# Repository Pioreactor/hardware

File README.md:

### HAT hardware setup

#### Installation

0. Install git: `sudo apt-get install git -y`
1. git clone this repo to your Raspberry Pi: `git clone --recurse-submodules https://github.com/Pioreactor/hardware.git && cd hardware`
2. Install eeprom utils: `cd hats/eepromutils && make && sudo make install && cd ..`
3. Move some files over: `mv ../eeprom/write_eeprom.py eepromutils/ && mv ../eeprom/pioreactor_eeprom_settings.txt.template eepromutils/`

#### Setting up a new HAT

0. Attach the HAT to the RPi.
1. Run `sudo bash setup_HAT.py`
2. Record the serial number/UUID
2. After a `sudo reboot`, try  `pio version -v` to confirm that HATs version.

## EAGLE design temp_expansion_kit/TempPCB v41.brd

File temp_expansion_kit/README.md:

# Temperature Expansion Kit

### Pt1000 probe and cable

Need a 3-wire Pt1000 probe with jst connector. 

We Purchased from [here](https://www.alibaba.com/product-detail/GAIMC-Customized-waterproof-ClassA-PT1000-PT100_1600338752153.html?spm=a2756.trade-list-buyer.0.0.289276e9jdTwxA) 

 - 5mm diameter 47mm length hot sleeve with g1/8 threads
 - 3mm diameter probe

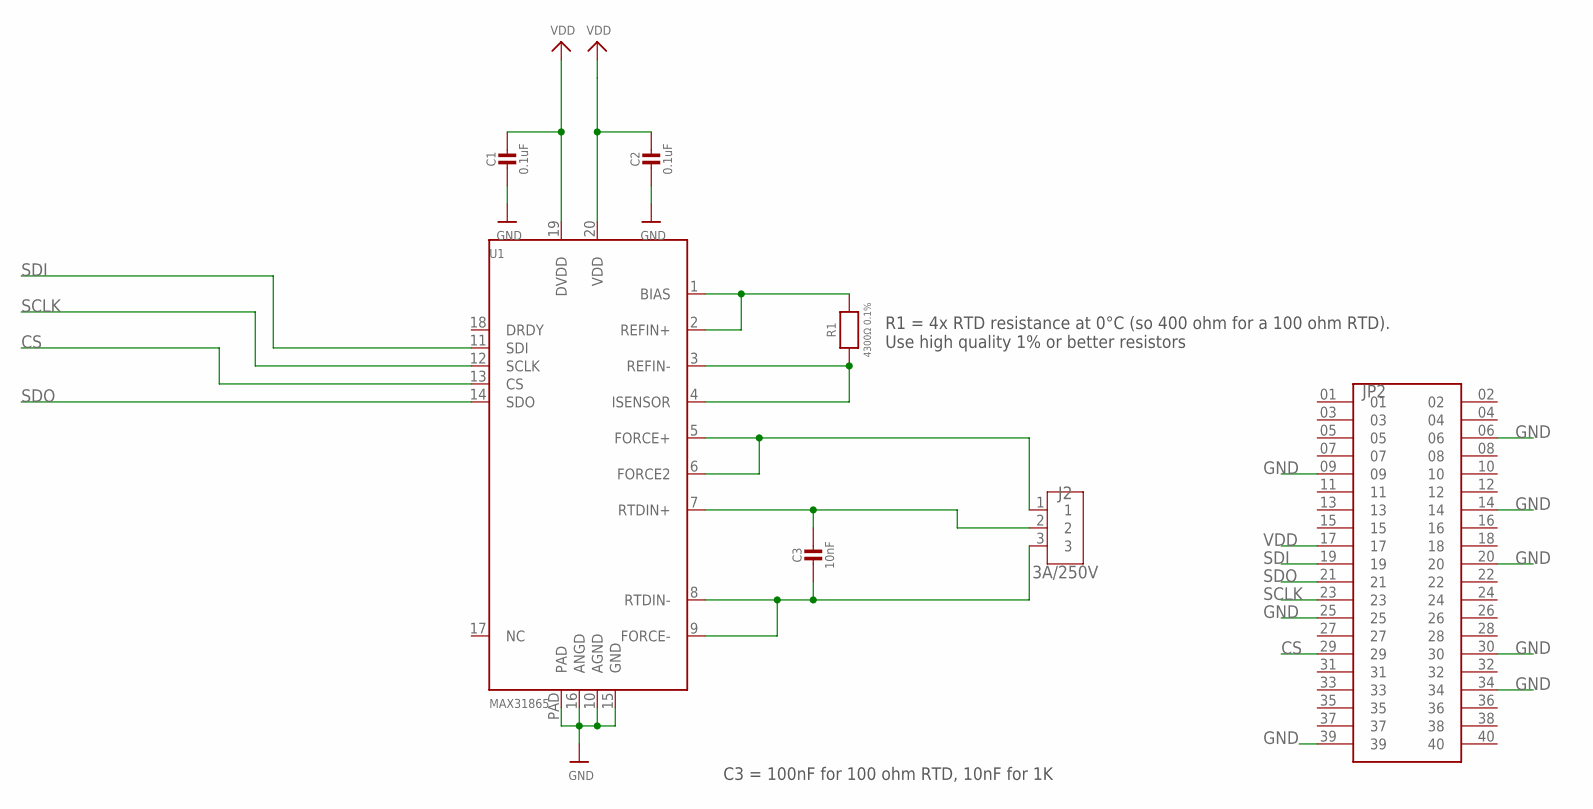
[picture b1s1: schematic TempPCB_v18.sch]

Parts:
C1, C2: 0.1uF; 0805-NO
C3: 10nF; 0805-NO
J2: 3A/250V; S3B-XH-A
JP2: SSQ-120-03-T-D; SAMTEC_SSQ-120-03-T-D
R1: 4300Ω 0.1%; 0805-NO
U1: MAX31865; QFN20_4MM_0.65MM

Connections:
CS: JP2.29, U1.13 (CS)
FORCE+: J2.1, U1.5 (FORCE+), U1.6 (FORCE2)
GND: C1.2, C2.2, JP2.06, JP2.09, JP2.14, JP2.20, JP2.25, JP2.30, JP2.34, JP2.39, U1.10 (AGND), U1.15 (GND), U1.16 (ANGD), U1.PAD
unnamed: R1.1, U1.3 (REFIN-), U1.4 (ISENSOR)
unnamed: R1.2, U1.1 (BIAS), U1.2 (REFIN+)
RTDIN+: C3.1, J2.2, U1.7 (RTDIN+)
RTDIN-: C3.2, J2.3, U1.8 (RTDIN-), U1.9 (FORCE-)
SCLK: JP2.23, U1.12 (SCLK)
SDI: JP2.19, U1.11 (SDI)
SDO: JP2.21, U1.14 (SDO)
VDD: C1.1, C2.1, JP2.17, U1.19 (DVDD), U1.20 (VDD)

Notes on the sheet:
C3 = 100nF for 100 ohm RTD, 10nF for 1K
R1 = 4x RTD resistance at 0°C (so 400 ohm for a 100 ohm RTD). Use high quality 1% or better resistors

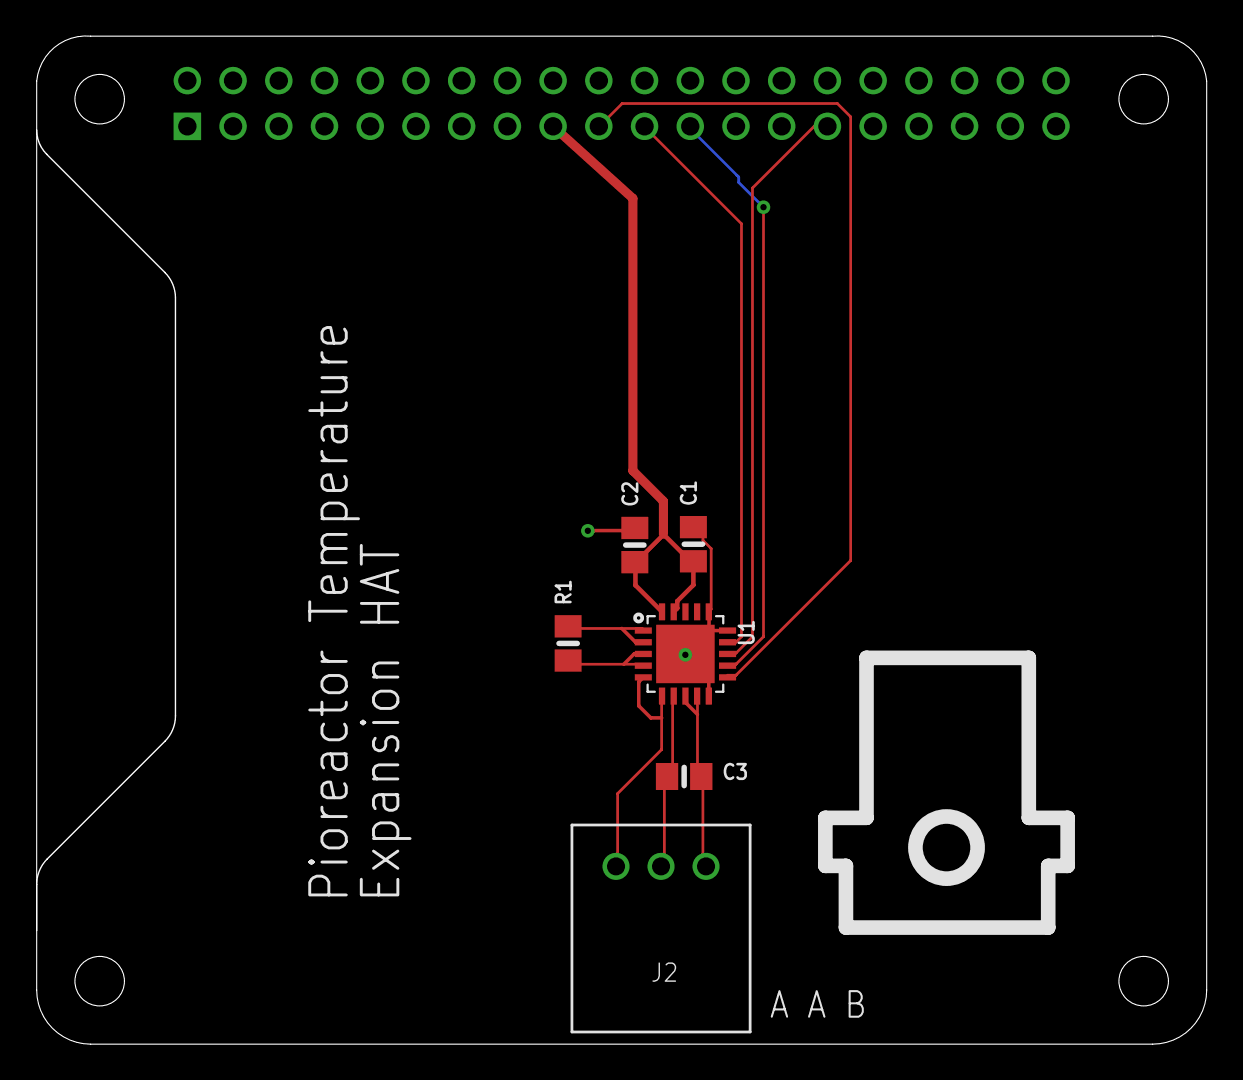
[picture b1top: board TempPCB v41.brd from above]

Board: 2 copper layers, 65.0 x 56.0 mm, 7 parts (1 on the bottom side), 11 nets.

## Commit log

2020-12-12 adding 3d files
2020-12-13 new holder with 8 angles
2020-12-14 shorter base
2021-12-14 adding eeprom file
2021-12-15 replace with template
2021-12-16 adding script to write our custom eeprom
2022-02-28 update here
2022-03-30 add more to eeprom
2022-08-22 small updates
2022-08-22 remove these; not using them anymore
2022-12-03 adding tests
2022-12-03 updates to write eeprom
2022-12-03 readme
2022-12-04 more
2022-12-04 adding hats repo as submodule
2022-12-04 top level readme
2023-02-16 fixes
2023-11-02 turn off leds after test
2023-11-21 update some testS
2023-11-23 testes
2024-01-09 adding heater for 20ml pioreactor
2024-04-27 Create LICENSE
2024-04-27 Update LICENSE
2024-07-29 adding assembly docs
2024-08-26 STEP files of hardware
2026-01-16 open source the temp hat
2026-01-16 cables
2026-04-15 step for eye-spy

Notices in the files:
parts and their libraries:
microbuilder: This work is placed in the public domain, and may be freely used for commercial and non-commercial work with the following conditions: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
